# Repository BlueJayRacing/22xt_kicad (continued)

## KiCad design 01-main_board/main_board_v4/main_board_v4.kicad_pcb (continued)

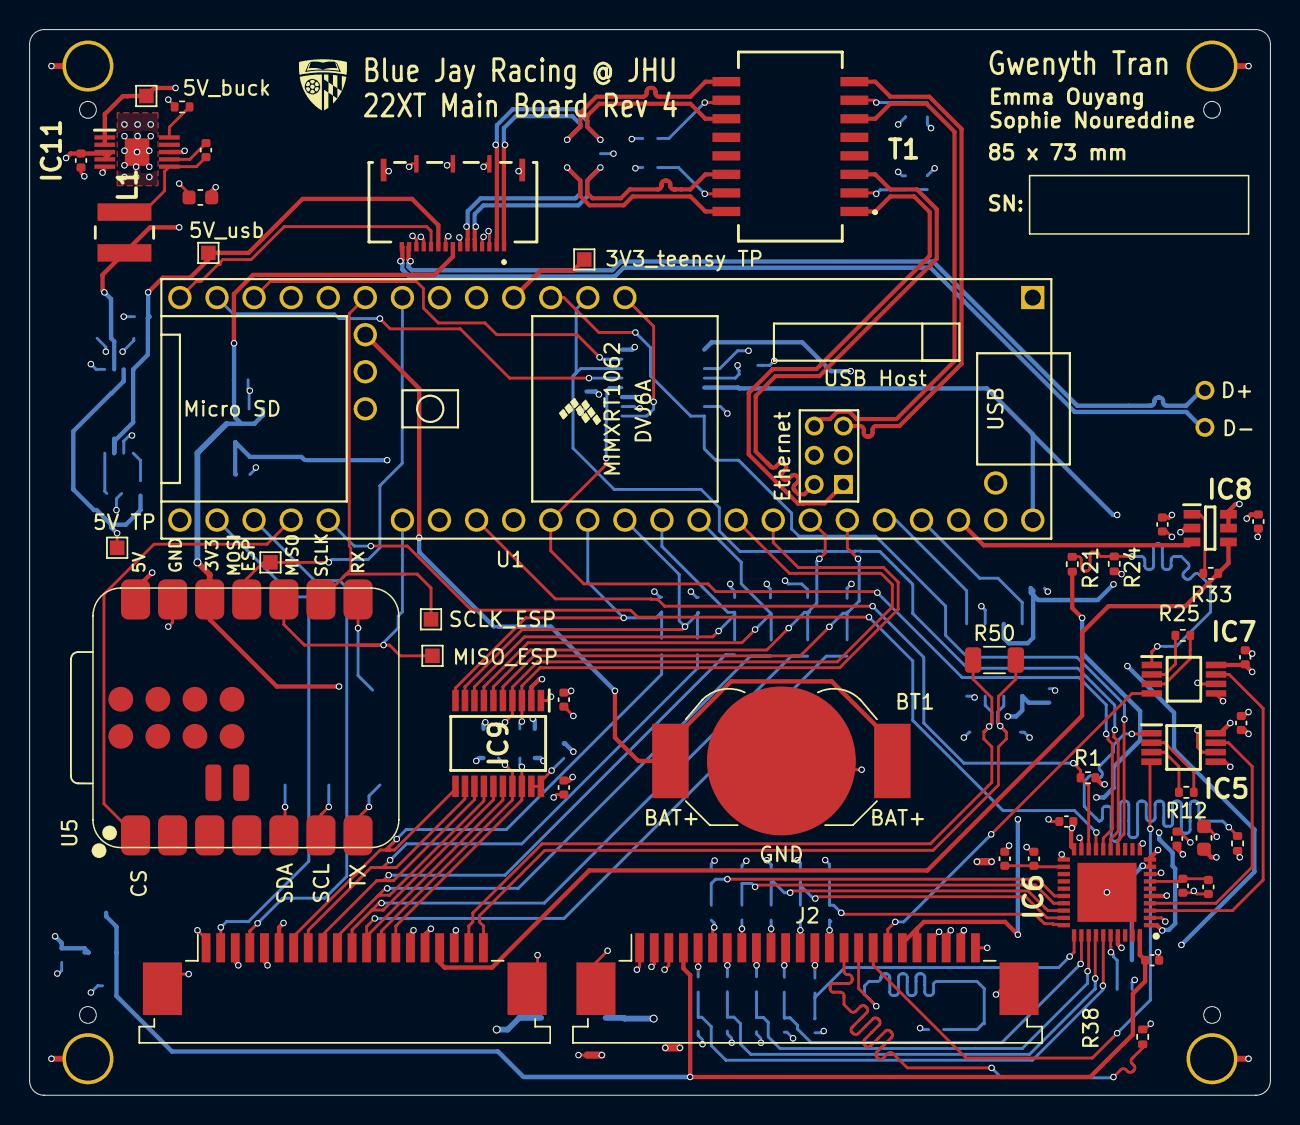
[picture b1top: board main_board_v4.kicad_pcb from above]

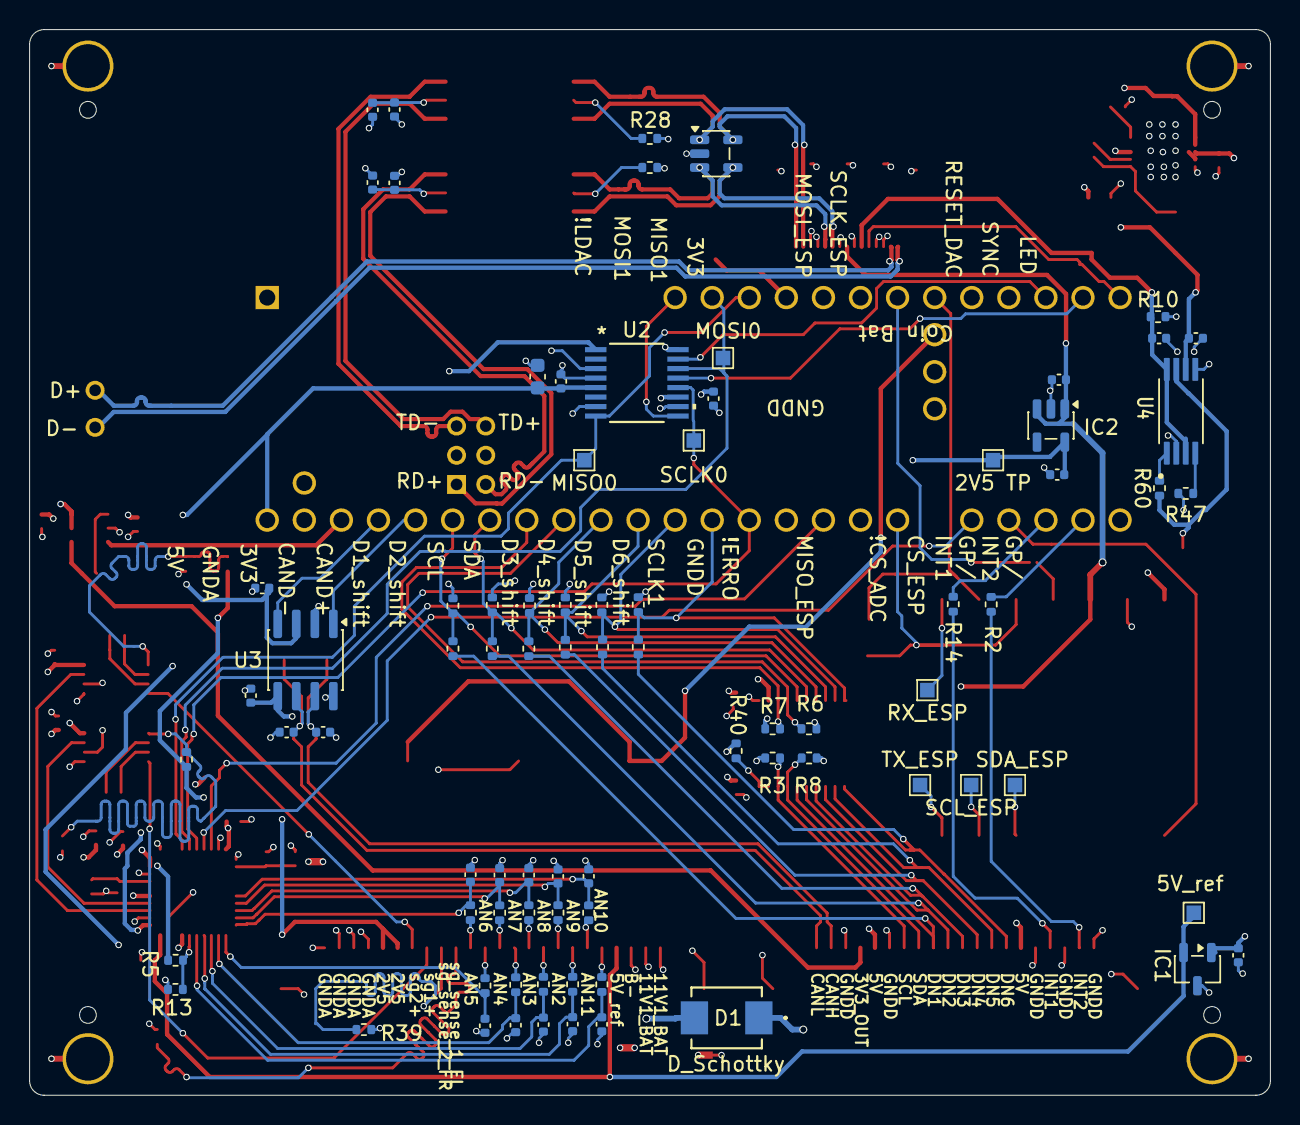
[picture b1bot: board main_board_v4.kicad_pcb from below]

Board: 4 copper layers, 85.0 x 73.0 mm, 139 parts (80 on the bottom side), 116 nets.

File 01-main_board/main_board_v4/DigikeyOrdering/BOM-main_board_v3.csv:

Comment,Designator,Footprint,LCSC,Quantity
1 uF,"C1,C2",C_0402_1005Metric,C52923,2
100R,R13,R_0402_1005Metric,C25076,1
100k,R60,R_0402_1005Metric,C25741,1
10k,R1,R_0402_1005Metric,C25744,1
10uF,"C11,C15",C_0603_1608Metric,C19702,2
120,R50,R_1206_3216Metric,C17909,1
1uF,"C13,C19",C_0402_1005Metric,C52923,2
200k,R40,R_0402_1005Metric,C25764,1
4.7uF,"C10,C36,C39",C_0402_1005Metric,C23733,3
AD7175-8BCPZ-RL7,IC6,QFN50P600X600X80-41N-D,C578395,1
5V TP,TP7,TestPoint_Pad_1.0x1.0mm,,1
LT3973EMSE-5#PBF,IC11,SOP50P490X110-11N,,1
0.47uF,C38,C_0402_1005Metric,,1
0.1uF,C40,C_0402_1005Metric,,1
0.1uF,C21,C_0402_1005Metric,,1
749013011,T1,749013011,,1
AD8591ARTZ-REEL7,IC8,SOT95P280X145-6N,,1
0.1uF,C20,C_0402_1005Metric,,1
120R (0.1%),R38,R_0402_1005Metric,,1
0.1uF,C16,C_0402_1005Metric,,1
120R (0.1%),R24,R_0402_1005Metric,,1
0.1uF,C26,C_0402_1005Metric,,1
INA827AIDGK,IC5,SOP65P490X110-8N,,1
MOSI,TP2,TestPoint_Pad_1.0x1.0mm,,1
0.1uF,C18,C_0402_1005Metric,,1
MISO_ESP,TP1,TestPoint_Pad_1.0x1.0mm,,1
0.1uF,C27,C_0402_1005Metric,,1
0.1uF,C23,C_0402_1005Metric,,1
215k,R9,R_0402_1005Metric,,1
0.1uF,C14,C_0402_1005Metric,,1
0.1uF,C8,C_0402_1005Metric,,1
120R (0.1%),R22,R_0402_1005Metric,,1
22uF,C61,C_0603_1608Metric,,1
80 (0.1%),R25,R_0402_1005Metric,,1
Battery_Cell,BT1,BatteryHolder_LINX_BAT-HLD-012-SMT,,1
120R (0.1%),R21,R_0402_1005Metric,,1
80 (0.1%),R12,R_0402_1005Metric,,1
0.1uF,C17,C_0402_1005Metric,,1
TPS2115APWR,U4,SOP65P640X120-8N,,1
0.1uF,C22,C_0402_1005Metric,,1
FFC Digital,J3,TE_2-84952-0_1x20-1MP_P1.0mm_Horizontal,,1
20R,R33,R_0402_1005Metric,,1
FFC Analog,J2,TE_2-84952-4_1x24-1MP_P1.0mm_Horizontal,,1
15uH,L1,NRS4012T150MDGJ,,1
SCLK_ESP,TP3,TestPoint_Pad_1.0x1.0mm,,1
400R,R47,R_0402_1005Metric,,1
3V3_teensy TP,TP10,TestPoint_Pad_1.0x1.0mm,,1
0.1uF,C9,C_0402_1005Metric,,1
INA827AIDGK,IC7,SOP65P490X110-8N,,1
XIAO-ESP32-S3,U5,XIAO-ESP32S3-SMD,,1
FFC Main to Peripheral,J4,FH4115S05SH05,,1
LSF0108PWR,IC9,SOP65P640X120-20N,,1
Teensy4.1,U1,Teensy41,,1
1.6k,R49,R_0402_1005Metric,,1
DNP,R17,R_0402_1005Metric,,1
1.6k,R65,R_0402_1005Metric,,1
52.3R,R27,R_0402_1005Metric,,1
1.69k,R3,R_0402_1005Metric,,1
MAX6105EUR+T,IC1,SOT-23-3,,1
DNP,R4,R_0402_1005Metric,,1
0.1uF,C3,C_0402_1005Metric,,1
MCP2562FD-E/SN,U3,SOIC-8_3.9x4.9mm_P1.27mm,,1
D_Schottky,D1,DO-214BA_MCH,,1
0.1uF,C45,C_0402_1005Metric,,1
DNP,R18,R_0402_1005Metric,,1
0.1uF,C29,C_0402_1005Metric,,1
DNP,R29,R_0402_1005Metric,,1
0.1uF,C12,C_0402_1005Metric,,1
LP5907MFX-2.5_NOPB,IC2,SOT-23-5,,1
1.6k,R44,R_0402_1005Metric,,1
52.3R,R28,R_0402_1005Metric,,1
0.1uF,C43,C_0402_1005Metric,,1
0.1uF,C42,C_0402_1005Metric,,1
DNP,R19,R_0402_1005Metric,,1
MISO1,TP4,TestPoint_Pad_1.0x1.0mm,,1
0.1uF,C35,C_0402_1005Metric,,1
DNP,R26,R_0402_1005Metric,,1
1.6k,R41,R_0402_1005Metric,,1
MOSI1,TP5,TestPoint_Pad_1.0x1.0mm,,1
DNP,R30,R_0402_1005Metric,,1
39pF,C51,C_0402_1005Metric,,1
39pF,C52,C_0402_1005Metric,,1
680R,R5,R_0402_1005Metric,,1
RCLAMP3354S.TCT,D2,SOT-23-5,,1
5V_ref,TP13,TestPoint_Pad_1.0x1.0mm,,1
0.1uF,C44,C_0402_1005Metric,,1
DNP,R16,R_0402_1005Metric,,1
AD5689RARUZ-RL7,U2,RU_16_ADI,,1
1.6k,R48,R_0402_1005Metric,,1
0.1uF,C46,C_0402_1005Metric,,1
1.07k,R7,R_0402_1005Metric,,1
1.6k,R43,R_0402_1005Metric,,1
120R (0.1%),R39,R_0402_1005Metric,,1
1.6k,R64,R_0402_1005Metric,,1
0.1uF,C34,C_0402_1005Metric,,1
SCLK1,TP6,TestPoint_Pad_1.0x1.0mm,,1
0.1uF,C32,C_0402_1005Metric,,1
47,R14,R_0402_1005Metric,,1
1.07k,R6,R_0402_1005Metric,,1
47,R2,R_0402_1005Metric,,1
1.69k,R8,R_0402_1005Metric,,1
1.6k,R46,R_0402_1005Metric,,1
0.1uF,C33,C_0402_1005Metric,,1
0.1uF,C41,C_0402_1005Metric,,1
0.1uF,C37,C_0402_1005Metric,,1
1.6k,R63,R_0402_1005Metric,,1
120R (0.1%),R20,R_0402_1005Metric,,1
0.1uF,C24,C_0402_1005Metric,,1
0.1uF,C28,C_0402_1005Metric,,1
0.1uF,C31,C_0402_1005Metric,,1
0.1uF,C4,C_0402_1005Metric,,1
DNP,R15,R_0402_1005Metric,,1
1.6k,R42,R_0402_1005Metric,,1
DNP,R34,R_0402_1005Metric,,1
DNP,R31,R_0402_1005Metric,,1
0.1uF,C30,C_0402_1005Metric,,1
DNP,R32,R_0402_1005Metric,,1
5V_usb,5v_usb,TestPoint_Pad_1.0x1.0mm,,1
5V_buck,5V_buck,TestPoint_Pad_1.0x1.0mm,,1
RX_ESP,RX_ESP,TestPoint_Pad_1.0x1.0mm,,1
TX_ESP,TX_ESP,TestPoint_Pad_1.0x1.0mm,,1
2V5 TP,2V5,TestPoint_Pad_1.0x1.0mm,,1
SDA_ESP,SDA_ESP,TestPoint_Pad_1.0x1.0mm,,1
SCL_ESP,SCL_ESP,TestPoint_Pad_1.0x1.0mm,,1

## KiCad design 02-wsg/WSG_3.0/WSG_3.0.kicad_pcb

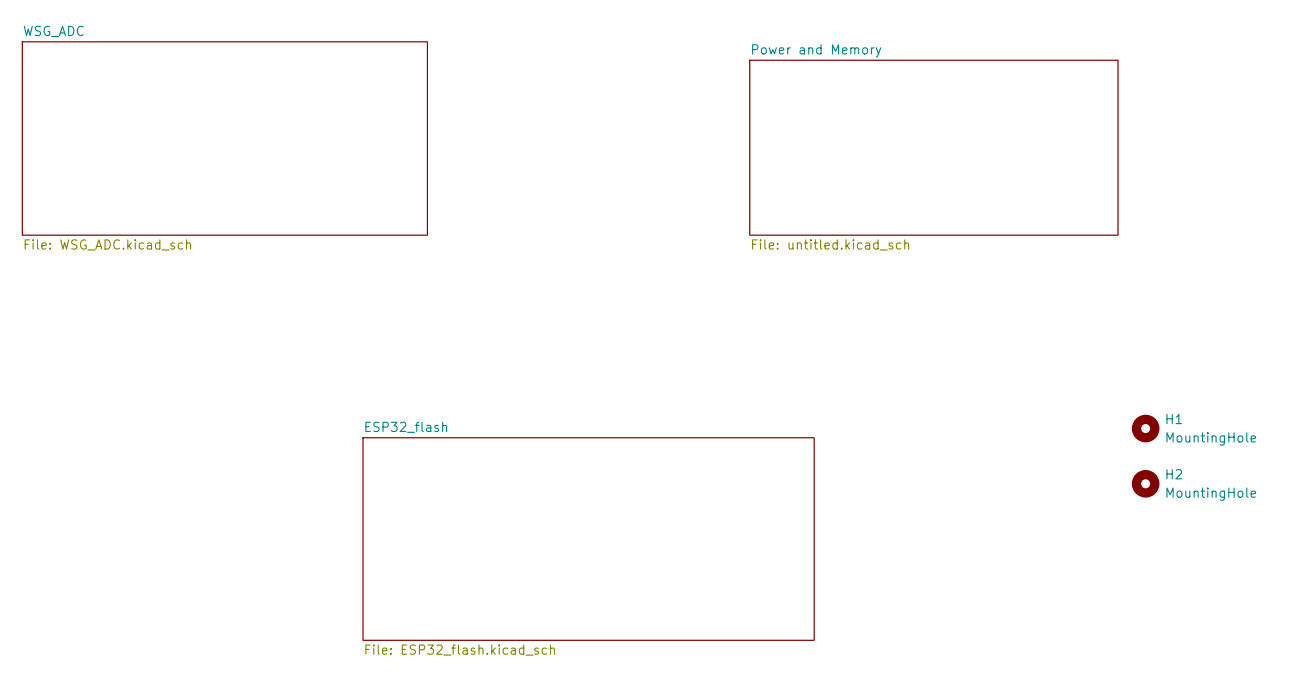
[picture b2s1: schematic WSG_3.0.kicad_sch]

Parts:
H1, H2: MountingHole; ToolingHole_1.152mm

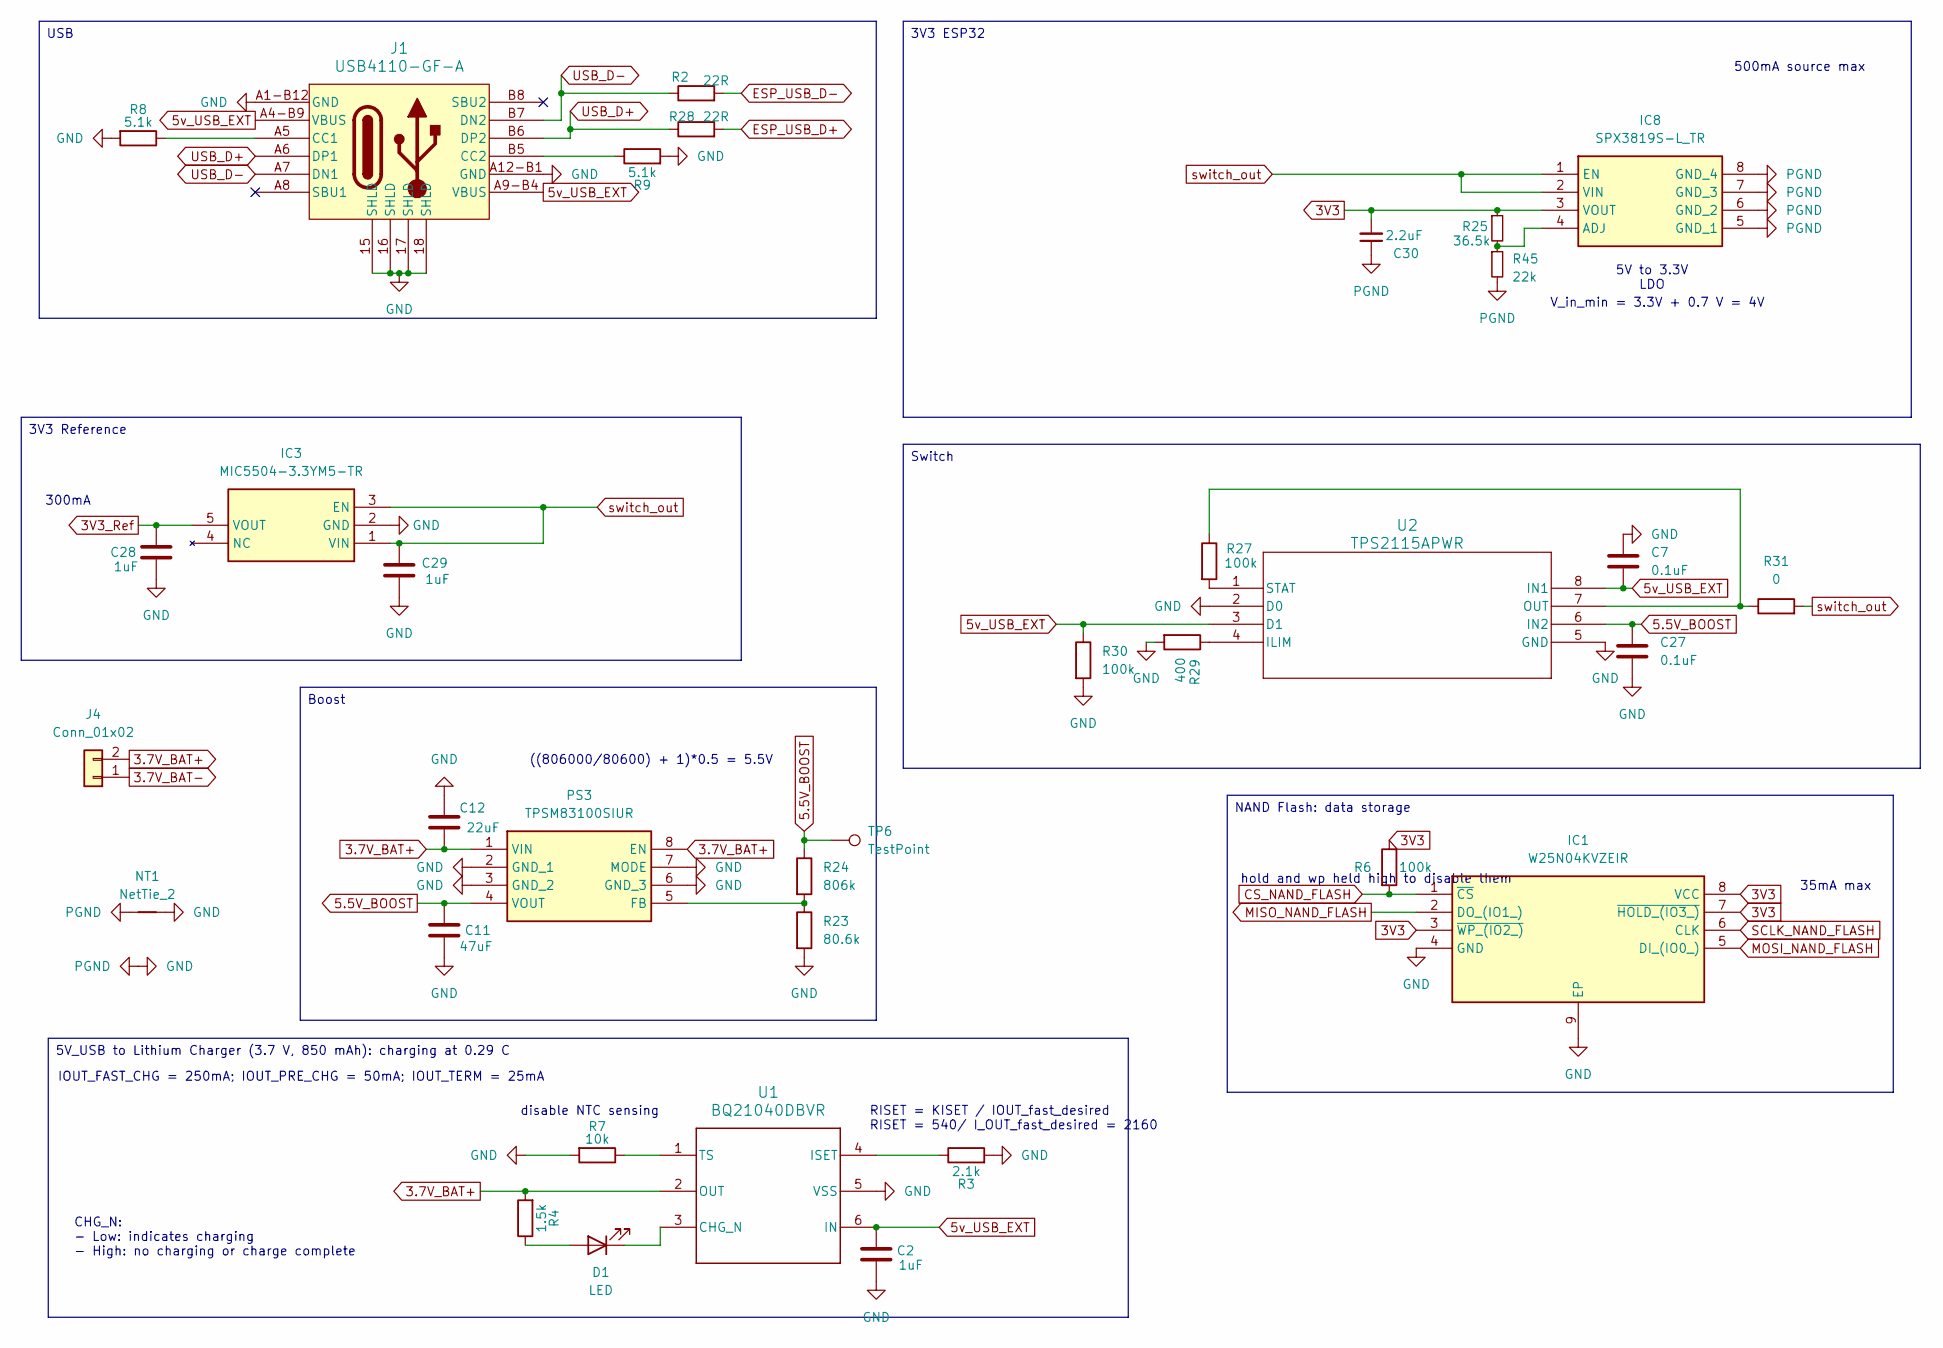
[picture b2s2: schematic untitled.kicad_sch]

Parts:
C2: 1uF; C_0603_1608Metric
C7, C27: 0.1uF; C_0402_1005Metric
C11: 47uF; C_0603_1608Metric
C12: 22uF; C_0603_1608Metric
C28, C29: 1uF; C_0402_1005Metric
C30: 2.2uF; C_0402_1005Metric
D1: LED; D_0402_1005Metric
IC1: W25N04KVZEIR; SON127P800X600X80-9N-D; Mouser Part Number 454-W25N04KVZEIR
IC3: MIC5504-3.3YM5-TR; MIC5501234 (3.3v ref); Mouser Part Number 998-MIC5504-3.3YM5TR
IC8: SPX3819S-L_TR; SOIC127P600X175-8N; Mouser Part Number 701-SPX3819S-L/TR
J1: USB4110-GF-A; USB4110-GF-A_GCT
J4: Conn_01x02; JST_S2B-PH-K-S_LF__SN_-2pin_male
NT1: NetTie_2
PS3: TPSM83100SIUR; Mouser Part Number 595-TPSM83100SIUR
R2, R28: 22R; R_0402_1005Metric
R3: 2.1k; R_0402_1005Metric
R4: 1.5k; R_0402_1005Metric
R6, R27, R30: 100k; R_0402_1005Metric
R7: 10k; R_0402_1005Metric
R8, R9: 5.1k; R_0402_1005Metric
R23: 80.6k; R_0402_1005Metric
R24: 806k; R_0402_1005Metric
R25: 36.5k; R_0402_1005Metric
R29: 400; R_0402_1005Metric
R31: 0; R_0402_1005Metric
R45: 22k; R_0402_1005Metric
TP6: TestPoint; TestPoint_Pad_1.0x1.0mm
U1: BQ21040DBVR
U2: TPS2115APWR; TPS2115APW

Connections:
3.7V_BAT+: C12.2, J4.2, PS3.1 (VIN), PS3.8 (EN), R4.2, U1.2 (OUT)
3.7V_BAT-: J4.1; also elsewhere on the board
3V3: C30.2, IC1.3 (~WP_(IO2_)), IC1.7 (~HOLD_(IO3_)), IC1.8 (VCC), IC8.3 (VOUT), R6.1, R25.1; also elsewhere on the board
3V3_Ref: C28.1, IC3.5 (VOUT); also elsewhere on the board
5.5V_BOOST: C11.1, C27.1, PS3.4 (VOUT), R24.1, TP6.1, U2.6 (IN2)
5v_USB_EXT: C2.1, C7.2, J1.A4-B9 (VBUS), J1.A9-B4 (VBUS), R30.1, U1.6 (IN), U2.3 (D1), U2.8 (IN1)
CS_NAND_FLASH: IC1.1 (~CS), R6.2; also elsewhere on the board
ESP_USB_D+: R28.2; also elsewhere on the board
ESP_USB_D-: R2.2; also elsewhere on the board
GND: C2.2, C7.1, C11.2, C12.1, C27.2, C28.2, C29.2, C30.1, IC1.4 (GND), IC1.9 (EP), IC3.2 (GND), IC8.5 (GND_1), IC8.6 (GND_2), IC8.7 (GND_3), IC8.8 (GND_4), J1.15 (SHLD), J1.16 (SHLD), J1.17 (SHLD), J1.18 (SHLD), J1.A1-B12 (GND), J1.A12-B1 (GND), NT1.1, NT1.2, PS3.2 (GND_1), PS3.3 (GND_2), PS3.6 (GND_3), PS3.7 (MODE), R3.2, R7.2, R8.2, R9.2, R23.2, R29.2, R30.2, R45.2, U1.5 (VSS), U2.2 (D0), U2.5 (GND); also elsewhere on the board
MISO_ADC: IC1.2 (DO_(IO1_)); also elsewhere on the board
MOSI_ADC: IC1.5 (DI_(IO0_)); also elsewhere on the board
unnamed: D1.2 (A), R4.1
unnamed: D1.1 (K), U1.3 (CHG_N)
unnamed: IC8.4 (ADJ), R25.2, R45.1
unnamed: J1.A5 (CC1), R8.1
unnamed: J1.B5 (CC2), R9.1
unnamed: PS3.5 (FB), R23.1, R24.2
unnamed: R3.1, U1.4 (ISET)
unnamed: R7.1, U1.1 (TS)
unnamed: R29.1, U2.4 (ILIM)
unnamed: R27.1, R31.1, U2.7 (OUT)
unnamed: R27.2, U2.1 (STAT)
SCLK_ADC: IC1.6 (CLK); also elsewhere on the board
USB_D+: J1.A6 (DP1), J1.B6 (DP2), R28.1
USB_D-: J1.A7 (DN1), J1.B7 (DN2), R2.1
switch_out: C29.1, IC3.1 (VIN), IC3.3 (EN), IC8.1 (EN), IC8.2 (VIN), R31.2

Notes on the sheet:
RISET = KISET / IOUT_fast_desired RISET = 540/ I_OUT_fast_desired = 2160
V_in_min = 3.3V + 0.7 V = 4V
500mA source max
((806000/80600) + 1)*0.5 = 5.5V
disable NTC sensing
hold and wp held high to disable them
5V to 3.3V LDO
IOUT_FAST_CHG = 250mA; IOUT_PRE_CHG = 50mA; IOUT_TERM = 25mA
35mA max
300mA
CHG_N: - Low: indicates charging - High: no charging or charge complete
Boost
Switch
USB
3V3 Reference
3V3 ESP32
NAND Flash: data storage
5V_USB to Lithium Charger (3.7 V, 850 mAh): charging at 0.29 C

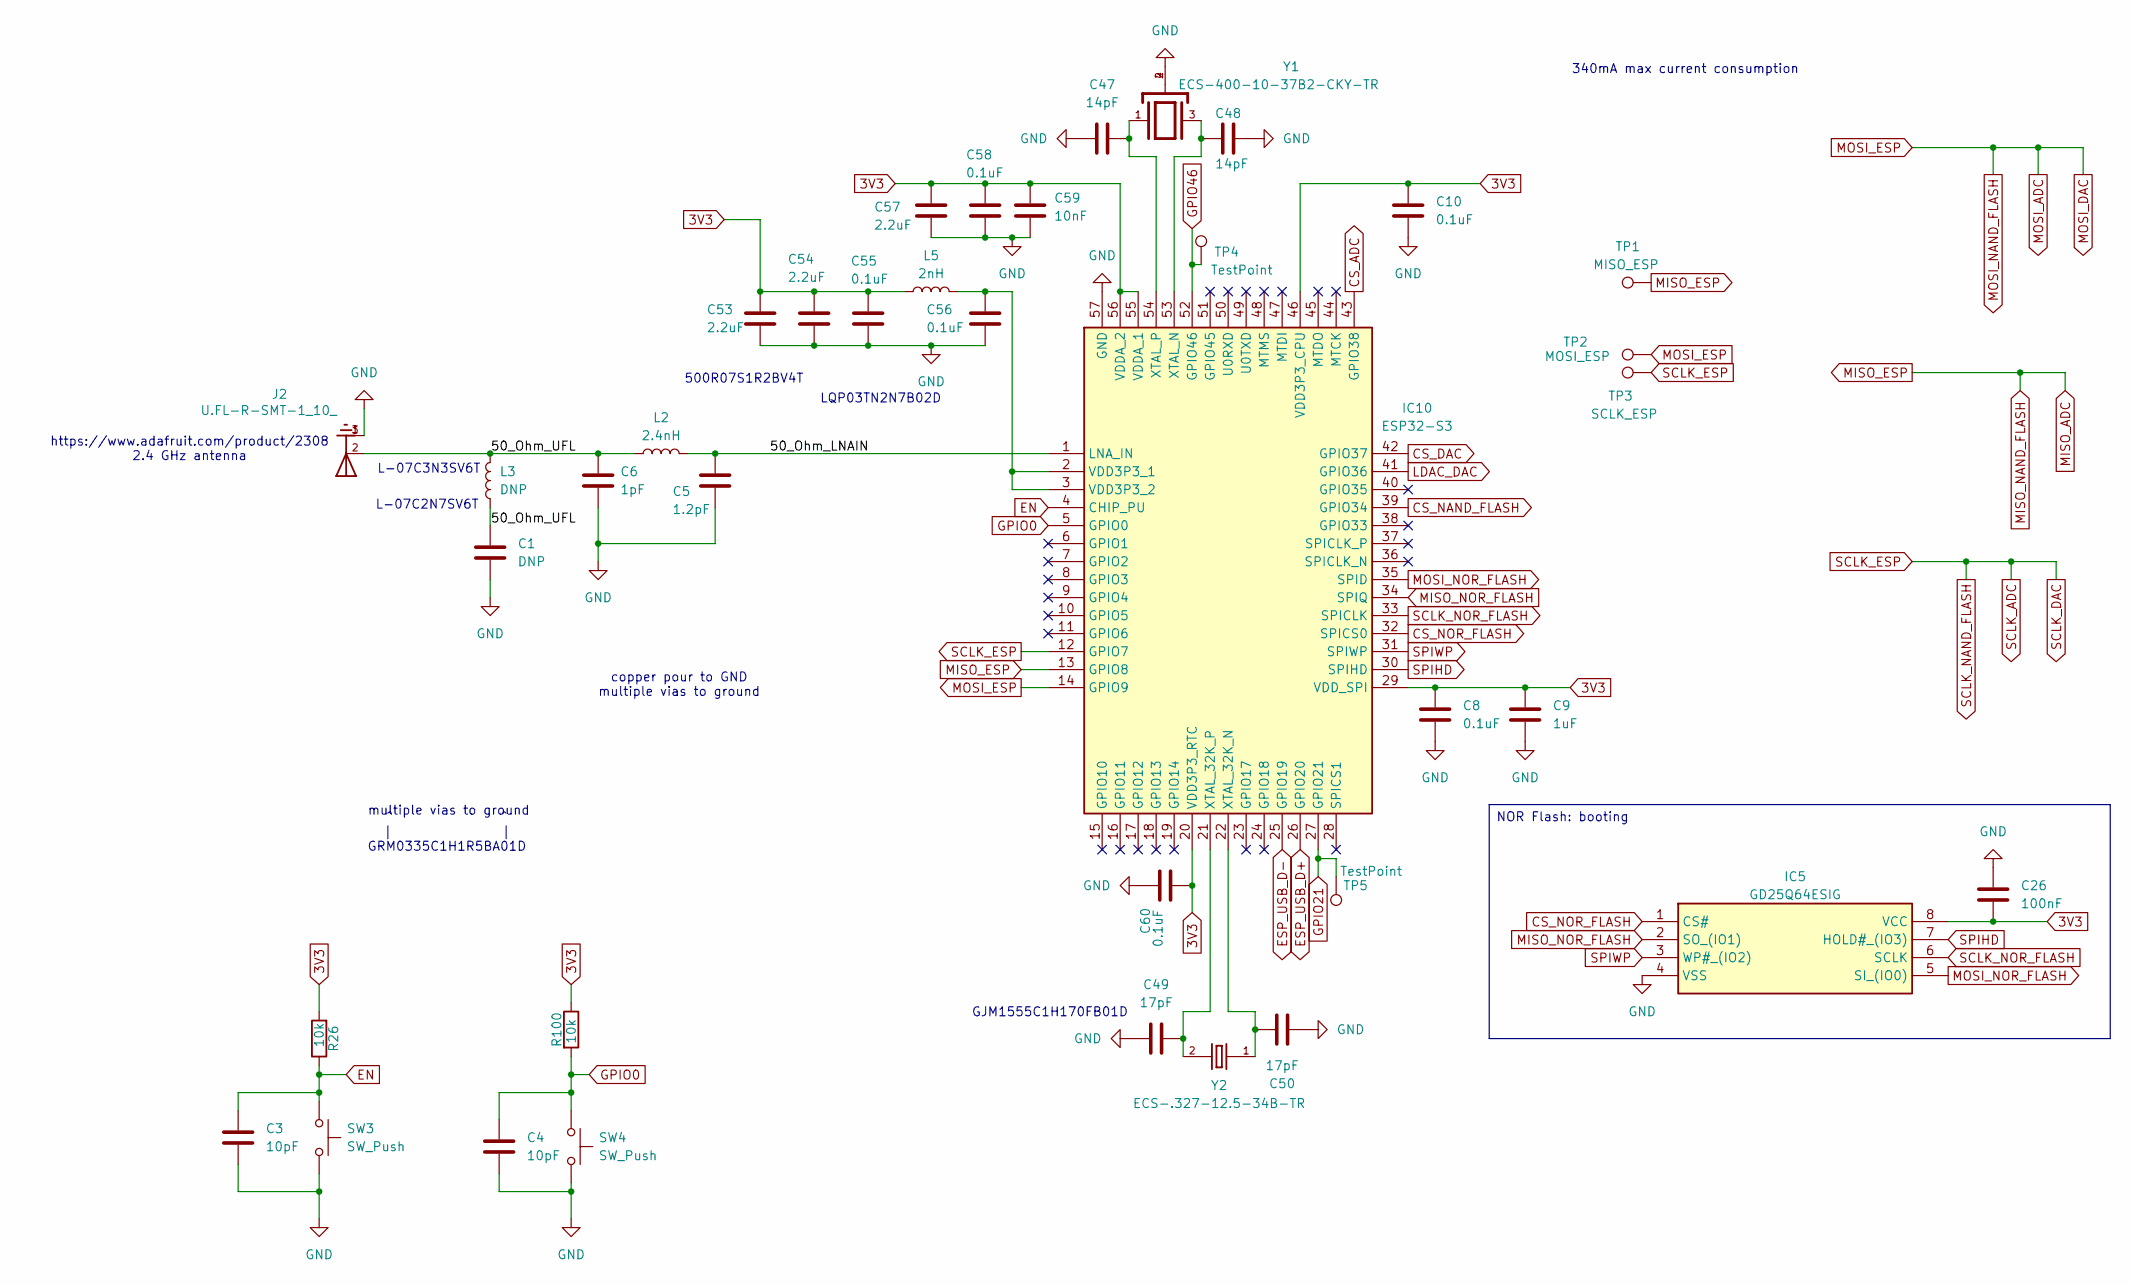
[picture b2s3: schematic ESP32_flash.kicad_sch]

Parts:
C1: DNP
C3, C4: 10pF; C_0402_1005Metric
C5: 1.2pF; C_0402_1005Metric
C6: 1pF; C_0402_1005Metric
C8, C10, C55, C56, C58, C60: 0.1uF; C_0402_1005Metric
C9: 1uF; C_0402_1005Metric
C26: 100nF; C_0402_1005Metric
C47, C48: 14pF; C_0402_1005Metric
C49, C50: 17pF; C_0402_1005Metric
C53, C54, C57: 2.2uF; C_0402_1005Metric
C59: 10nF; C_0402_1005Metric
IC5: GD25Q64ESIG; Mouser Part Number 363-GD25Q64ESIG
IC10: ESP32-S3; ESP32-S2FH2; Mouser Part Number 356-ESP32-S3
J2: U.FL-R-SMT-1_10_; HRS_U.FL-R-SMT-1_10_antenna
L2: 2.4nH; L_0402_1005Metric
L3: DNP; L_0402_1005Metric
L5: 2nH; L_0402_1005Metric
R26, R100: 10k; R_0402_1005Metric
SW3, SW4: SW_Push; NANOT100AS_butt
TP1: MISO_ESP; TestPoint_Pad_1.0x1.0mm
TP2: MOSI_ESP; TestPoint_Pad_1.0x1.0mm
TP3: SCLK_ESP; TestPoint_Pad_1.0x1.0mm
TP4, TP5: TestPoint; TestPoint_Pad_1.0x1.0mm
Y1: ECS-400-10-37B2-CKY-TR; XTAL_ECS-400-10-37B2-CKY-TR; PARTREV 2021
Y2: ECS-.327-12.5-34B-TR; XTAL_ECS-.327-12.5-34B-TR

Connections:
3V3: C8.1, C9.1, C10.1, C26.2, C53.1, C54.1, C55.1, C57.1, C58.1, C59.1, C60.1, IC5.8 (VCC), IC10.20 (VDD3P3_RTC), IC10.29 (VDD_SPI), IC10.46 (VDD3P3_CPU), IC10.55 (VDDA_1), IC10.56 (VDDA_2), L5.1, R26.2, R100.1; also elsewhere on the board
/ESP32_flash/50_Ohm_LNAIN: C5.1, IC10.1 (LNA_IN), L2.2
/ESP32_flash/50_Ohm_UFL: C1.1, C6.1, J2.2, L2.1, L3.1, L3.2
CS_ADC: IC10.43 (GPIO38); also elsewhere on the board
CS_DAC: IC10.42 (GPIO37); also elsewhere on the board
CS_NAND_FLASH: IC10.39 (GPIO34); also elsewhere on the board
CS_NOR_FLASH: IC5.1 (CS#), IC10.32 (SPICS0)
EN: C3.1, IC10.4 (CHIP_PU), R26.1, SW3.1
ESP_USB_D+: IC10.26 (GPIO20); also elsewhere on the board
ESP_USB_D-: IC10.25 (GPIO19); also elsewhere on the board
GND: C1.2, C3.2, C4.2, C5.2, C6.2, C8.2, C9.2, C10.2, C26.1, C47.2, C48.2, C49.2, C50.2, C53.2, C54.2, C55.2, C56.2, C57.2, C58.2, C59.2, C60.2, IC5.4 (VSS), IC10.57 (GND), J2.1, J2.3, SW3.2, SW4.2, Y1.2, Y1.4; also elsewhere on the board
GPIO0: C4.1, IC10.5 (GPIO0), R100.2, SW4.1
GPIO21: IC10.27 (GPIO21), TP5.1; also elsewhere on the board
GPIO46: IC10.52 (GPIO46), TP4.1
LDAC_DAC: IC10.41 (GPIO36); also elsewhere on the board
MISO_ADC: IC10.13 (GPIO8), TP1.1; also elsewhere on the board
MISO_NOR_FLASH: IC5.2 (SO_(IO1)), IC10.34 (SPIQ)
MOSI_ADC: IC10.14 (GPIO9), TP2.1; also elsewhere on the board
MOSI_NOR_FLASH: IC5.5 (SI_(IO0)), IC10.35 (SPID)
unnamed: C56.1, IC10.2 (VDD3P3_1), IC10.3 (VDD3P3_2), L5.2
unnamed: C50.1, IC10.22 (XTAL_32K_N), Y2.1
unnamed: C49.1, IC10.21 (XTAL_32K_P), Y2.2
unnamed: C48.1, IC10.53 (XTAL_N), Y1.3
unnamed: C47.1, IC10.54 (XTAL_P), Y1.1
SCLK_ADC: IC10.12 (GPIO7), TP3.1; also elsewhere on the board
SCLK_NOR_FLASH: IC5.6 (SCLK), IC10.33 (SPICLK)
SPIHD: IC5.7 (HOLD#_(IO3)), IC10.30 (SPIHD)
SPIWP: IC5.3 (WP#_(IO2)), IC10.31 (SPIWP)

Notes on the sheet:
^ ^ | | GRM0335C1H1R5BA01D
340mA max current consumption
copper pour to GND multiple vias to ground
L-07C3N3SV6T
LQP03TN2N7B02D
L-07C2N7SV6T
multiple vias to ground
https://www.adafruit.com/product/2308 2.4 GHz antenna
GJM1555C1H170FB01D
500R07S1R2BV4T
NOR Flash: booting

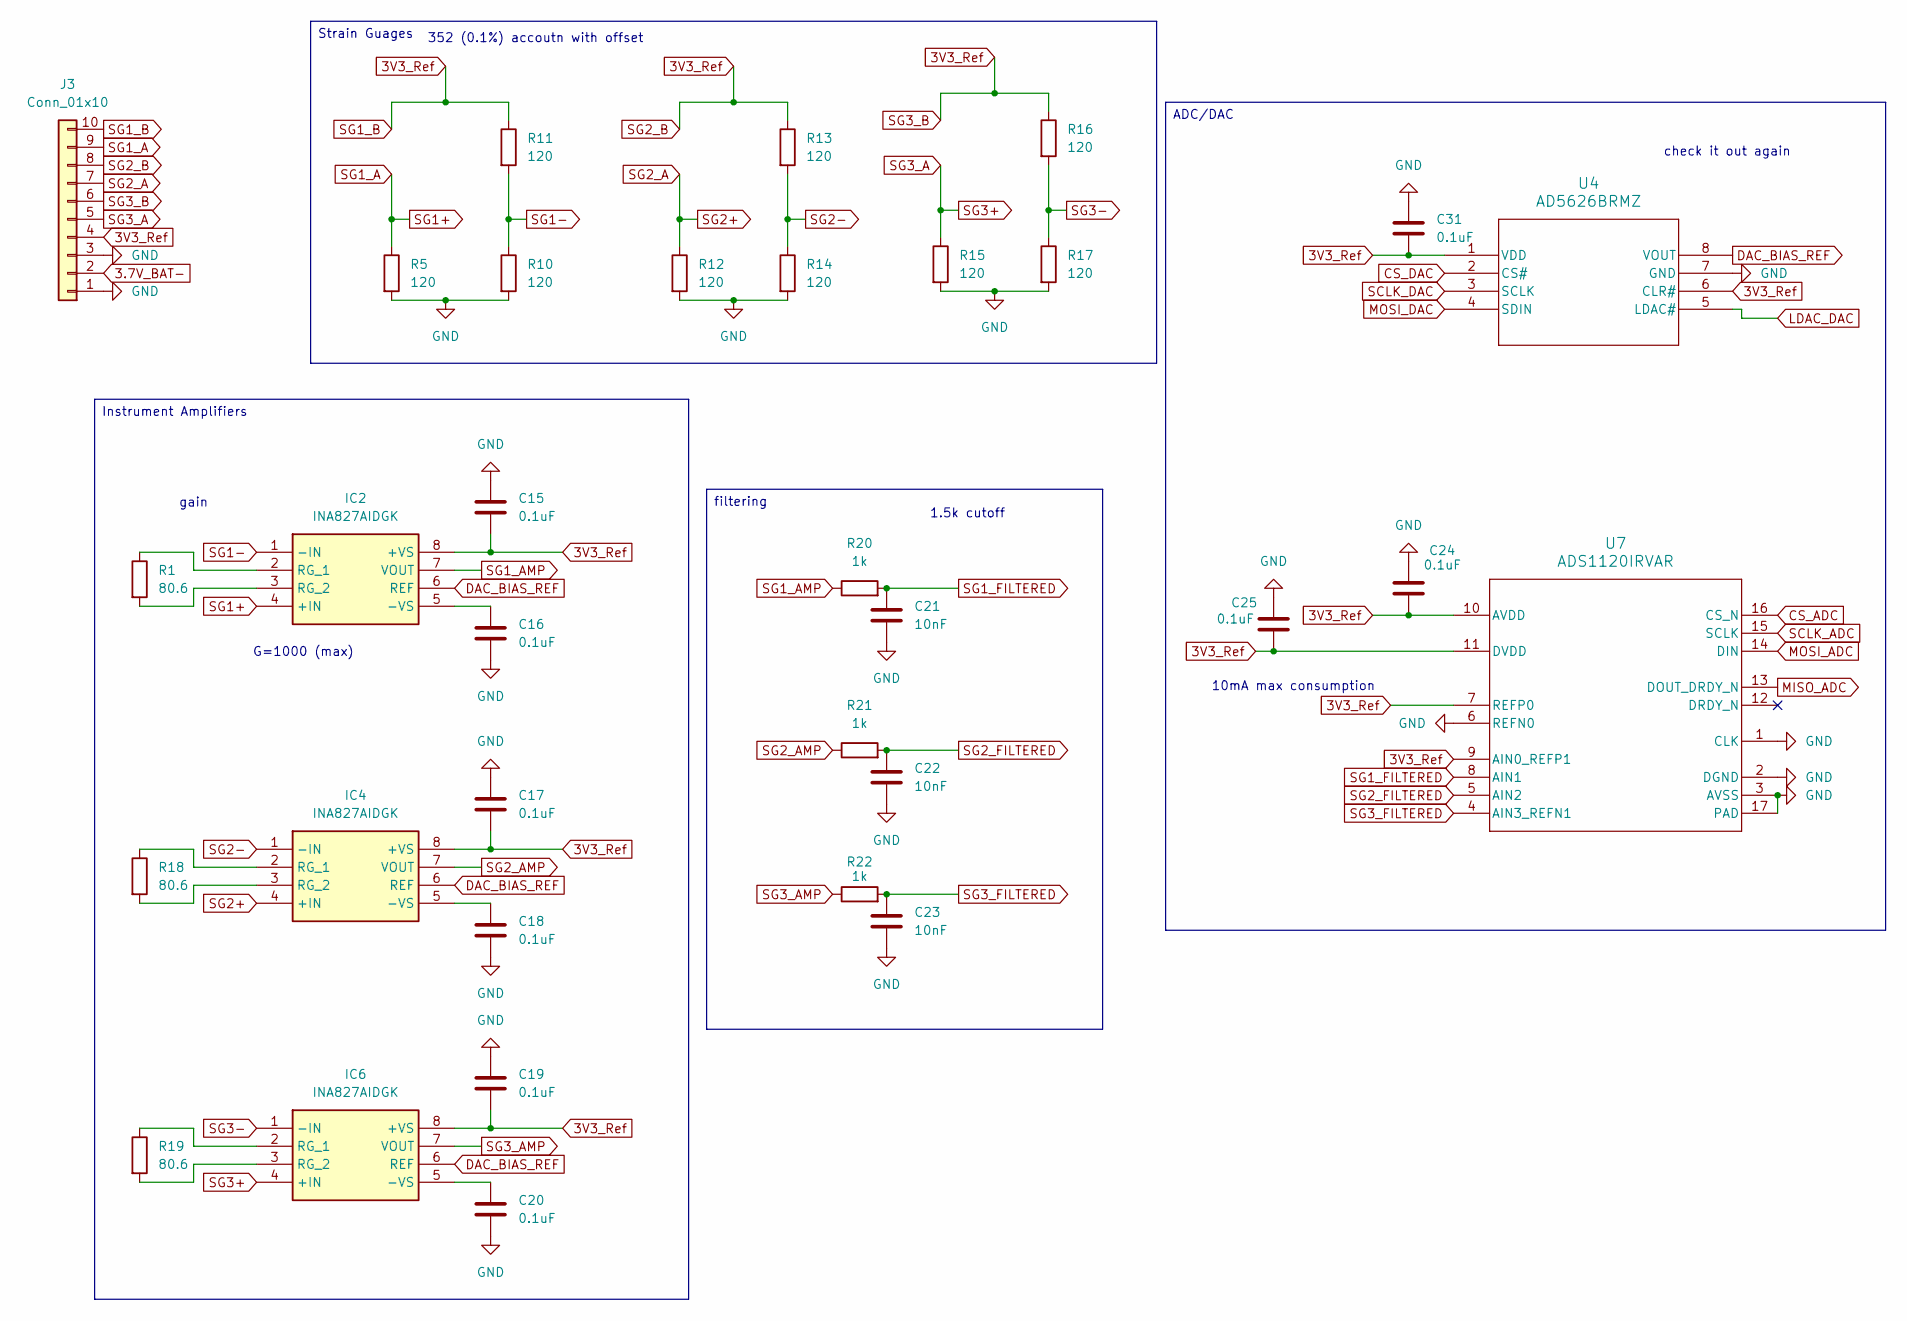
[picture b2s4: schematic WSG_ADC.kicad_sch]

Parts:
C15, C16, C17, C18, C19, C20, C24, C25, C31: 0.1uF; C_0402_1005Metric
C21, C22, C23: 10nF; C_0402_1005Metric
IC2, IC4, IC6: INA827AIDGK; Mouser Part Number 595-INA827AIDGK
J3: Conn_01x10; PinSocket_2x05_P2.00mm_Horizontal
R1, R18, R19: 80.6; R_0402_1005Metric
R5, R10, R11, R12, R13, R14, R15, R16, R17: 120; R_0402_1005Metric
R20, R21, R22: 1k; R_0402_1005Metric
U4: AD5626BRMZ; SOP65P490X110-8N
U7: ADS1120IRVAR; QFN50P350X350X100-17N-D

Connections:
3.7V_BAT-: J3.2; also elsewhere on the board
3V3_Ref: C15.2, C17.2, C19.2, C24.2, C25.2, C31.2, IC2.8 (+VS), IC4.8 (+VS), IC6.8 (+VS), J3.4, J3.6, J3.8, J3.10, R11.1, R13.1, R16.1, U4.1 (VDD), U4.6 (CLR#), U7.7 (REFP0), U7.9 (AIN0_REFP1), U7.10 (AVDD), U7.11 (DVDD); also elsewhere on the board
CS_ADC: U7.16 (CS_N); also elsewhere on the board
CS_DAC: U4.2 (CS#); also elsewhere on the board
DAC_BIAS_REF: IC2.6 (REF), IC4.6 (REF), IC6.6 (REF), U4.8 (VOUT)
GND: C15.1, C16.2, C17.1, C18.2, C19.1, C20.2, C21.2, C22.2, C23.2, C24.1, C25.1, C31.1, J3.1, J3.3, R5.2, R10.2, R12.2, R14.2, R15.2, R17.2, U4.7 (GND), U7.1 (CLK), U7.2 (DGND), U7.3 (AVSS), U7.6 (REFN0), U7.17 (PAD); also elsewhere on the board
LDAC_DAC: U4.5 (LDAC#); also elsewhere on the board
MISO_ADC: U7.13 (DOUT_DRDY_N); also elsewhere on the board
MOSI_ADC: U4.4 (SDIN), U7.14 (DIN); also elsewhere on the board
unnamed: C16.1, IC2.5 (-VS)
unnamed: IC2.2 (RG_1), R1.1
unnamed: IC2.3 (RG_2), R1.2
unnamed: C18.1, IC4.5 (-VS)
unnamed: IC4.2 (RG_1), R18.1
unnamed: IC4.3 (RG_2), R18.2
unnamed: C20.1, IC6.5 (-VS)
unnamed: IC6.2 (RG_1), R19.1
unnamed: IC6.3 (RG_2), R19.2
SCLK_ADC: U4.3 (SCLK), U7.15 (SCLK); also elsewhere on the board
SG1+: IC2.4 (+IN), J3.9, R5.1
SG1-: IC2.1 (-IN), R10.1, R11.2
SG1_AMP: IC2.7 (VOUT), R20.1
SG1_FILTERED: C21.1, R20.2, U7.8 (AIN1)
SG2+: IC4.4 (+IN), J3.7, R12.1
SG2-: IC4.1 (-IN), R13.2, R14.1
SG2_AMP: IC4.7 (VOUT), R21.1
SG2_FILTERED: C22.1, R21.2, U7.5 (AIN2)
SG3+: IC6.4 (+IN), J3.5, R15.1
SG3-: IC6.1 (-IN), R16.2, R17.1
SG3_AMP: IC6.7 (VOUT), R22.1
SG3_FILTERED: C23.1, R22.2, U7.4 (AIN3_REFN1)

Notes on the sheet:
1.5k cutoff
352 (0.1%) accoutn with offset
gain
10mA max consumption
G=1000 (max)
check it out again
ADC/DAC
filtering
Strain Guages
Instrument Amplifiers

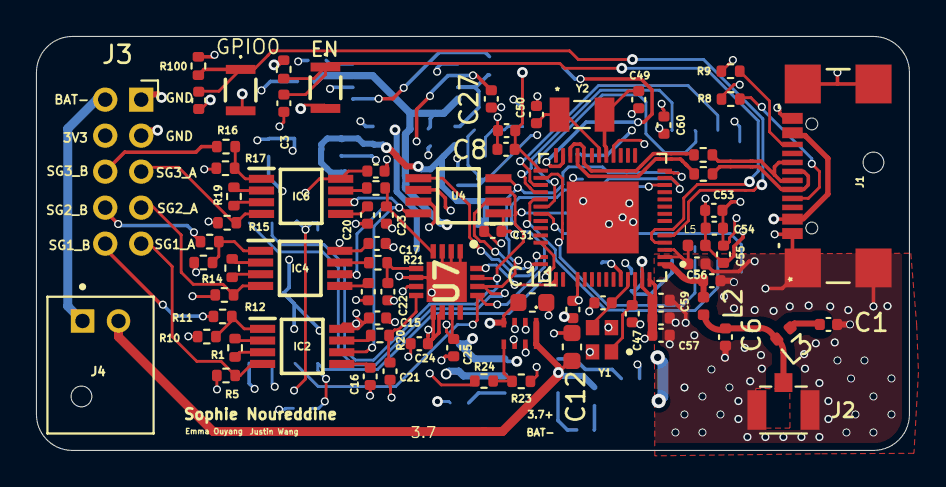
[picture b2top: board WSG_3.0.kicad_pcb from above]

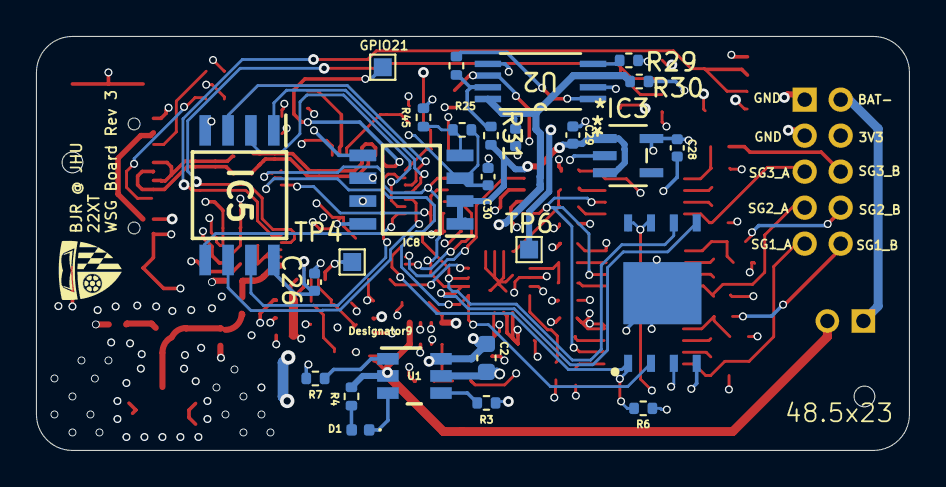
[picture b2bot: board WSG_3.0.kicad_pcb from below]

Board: 4 copper layers, 48.5 x 23.0 mm, 104 parts (26 on the bottom side), 69 nets.

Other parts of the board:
GPIO21: TestPoint; TestPoint_Pad_1.0x1.0mm

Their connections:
GPIO21: GPIO21.1; also elsewhere on the board

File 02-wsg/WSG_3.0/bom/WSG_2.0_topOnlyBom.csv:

Comment,Designator,Footprint,LCSC
Antenna_Chip,AE1,wsg_fp:XDCR_2450AT18B100E,
1.2pF,C1,Capacitor_SMD:C_0402_1005Metric,
47uF,C11,Capacitor_SMD:C_0402_1005Metric,
22uF,C12,Capacitor_SMD:C_0402_1005Metric,
1uF,"C9,C28,C29",Capacitor_SMD:C_0402_1005Metric,
0.1uF,"C8,C10,C15,C16,C17,C18,C19,C20,C24,C25,C31,C55,C56,C58,C60",Capacitor_SMD:C_0402_1005Metric,
10nF,"C21,C22,C23,C59",Capacitor_SMD:C_0402_1005Metric,
10pF,"C3,C4,C7",Capacitor_SMD:C_0402_1005Metric,
2.2uF,"C30,C53,C54,C57",Capacitor_SMD:C_0402_1005Metric,
14pF,"C47,C48",Capacitor_SMD:C_0402_1005Metric,
17pF,"C49,C50",Capacitor_SMD:C_0402_1005Metric,
1.5pF,"C5,C6",Capacitor_SMD:C_0402_1005Metric,
ESP32-S3,IC10,wsg_fp:ESP32-S2FH2,
INA827AIDGK,"IC2,IC4,IC6",wsg_fp:INA827AIDGK,
USB4110-GF-A,J1,wsg_fp:USB4110-GF-A_GCT,
Conn_01x08,J3,wsg_fp:M12A-08PFFP-SF8001,
Conn_01x02,J4,Connector_PinHeader_1.00mm:PinHeader_1x02_P1.00mm_Horizontal,
2.7nH,"L2,L3",Inductor_SMD:L_0402_1005Metric,
3.3nH,L4,Inductor_SMD:L_0402_1005Metric,
2nH,L5,Inductor_SMD:L_0402_1005Metric,
TPSM83100SIUR,PS3,wsg_fp:TPSM83100SIUR,
200,"R1,R18,R19",Resistor_SMD:R_0402_1005Metric,
22R,"R2,R28",Resistor_SMD:R_0402_1005Metric,
1k,"R20,R21,R22",Resistor_SMD:R_0402_1005Metric,
80.6k,R23,Resistor_SMD:R_0402_1005Metric,
806k,R24,Resistor_SMD:R_0402_1005Metric,
22k,R45,Resistor_SMD:R_0402_1005Metric,
120,"R5,R10,R11,R12,R13,R14,R15,R16,R17",Resistor_SMD:R_0402_1005Metric,
10k,"R26,R27,R100",Resistor_SMD:R_0402_1005Metric,
5.1k,"R8,R9",Resistor_SMD:R_0402_1005Metric,
SW_Push,"SW1,SW3,SW4",wsg_fp:NANOT100AS_butt,
AD5626BRMZ,U4,wsg_fp:SOP65P490X110-8N,
ADS1120IRVAR,U7,22xt_wsg_footprints:QFN50P350X350X100-17N-D,
ECS-400-10-37B2-CKY-TR,Y1,wsg_fp:XTAL_ECS-400-10-37B2-CKY-TR,
ECS-.327-12.5-34B-TR,Y2,wsg_fp:XTAL_ECS-.327-12.5-34B-TR,
